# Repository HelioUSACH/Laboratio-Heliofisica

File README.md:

Rama principal "Main"
Subir avances en ramas secundarias que se deben crear

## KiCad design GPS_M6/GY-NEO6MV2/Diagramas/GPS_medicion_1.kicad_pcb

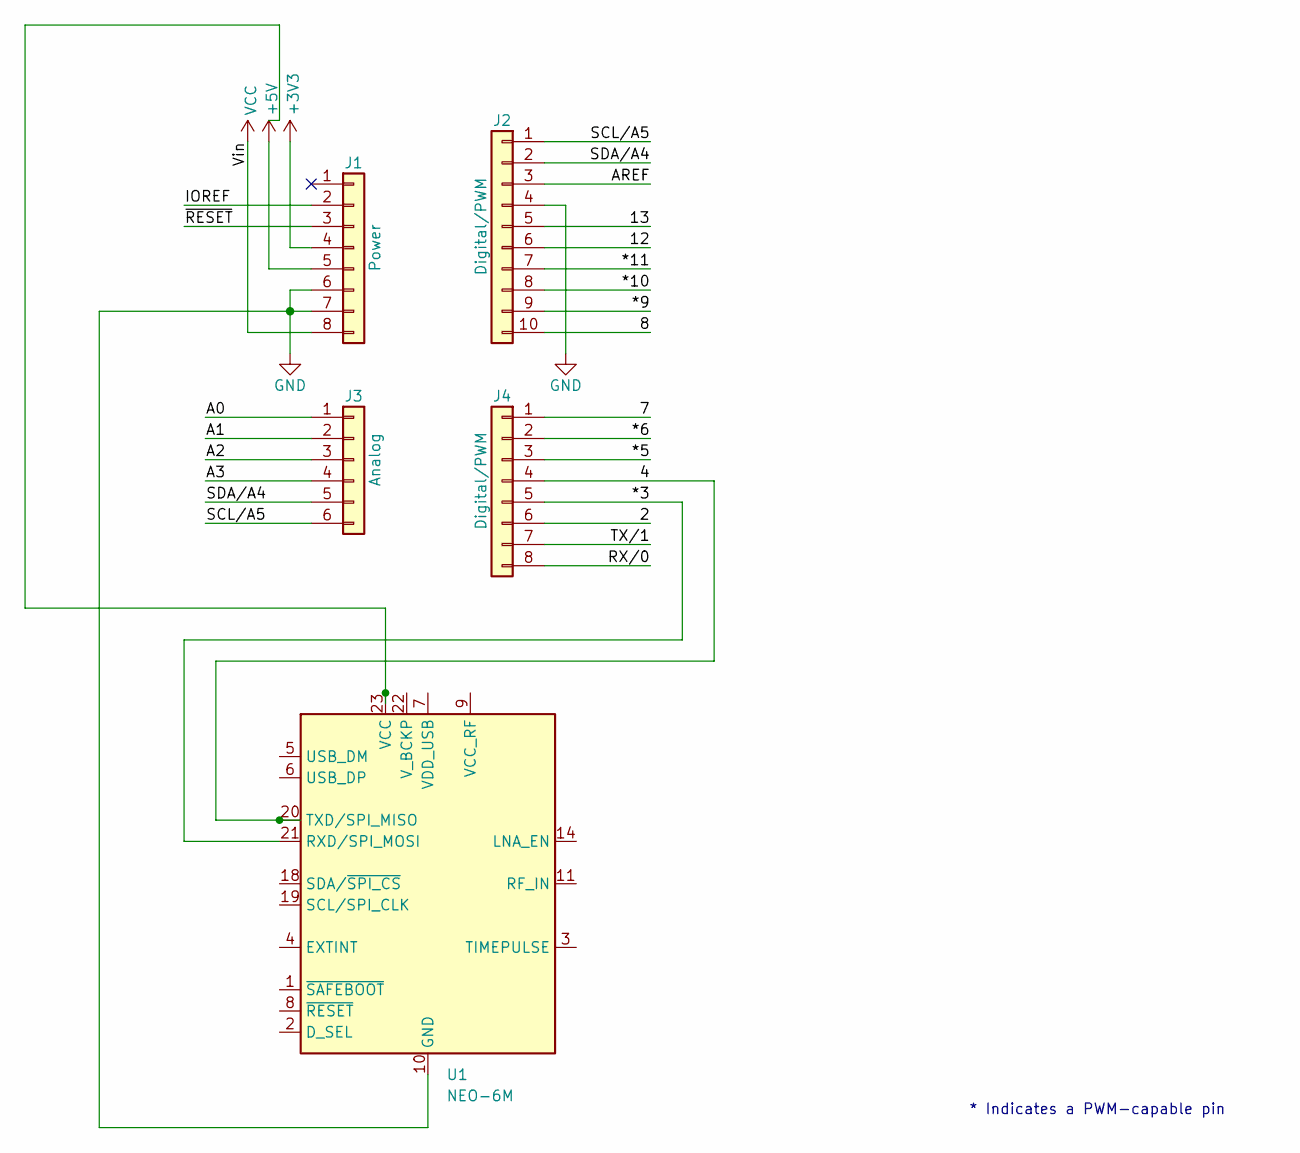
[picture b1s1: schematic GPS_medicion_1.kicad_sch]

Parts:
J1: Power; PinSocket_1x08_P2.54mm_Vertical
J2: Digital/PWM; PinSocket_1x10_P2.54mm_Vertical
J3: Analog; PinSocket_1x06_P2.54mm_Vertical
J4: Digital/PWM; PinSocket_1x08_P2.54mm_Vertical
U1: NEO-6M; ublox_NEO

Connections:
+3V3: J1.4
+5V: J1.5
/2: J4.6
/4: J4.4, U1.20 (TXD/SPI_MISO)
/7: J4.1
/8: J2.10
/12: J2.6
/13: J2.5
/*3: J4.5, U1.21 (RXD/SPI_MOSI)
/*5: J4.3
/*6: J4.2
/*9: J2.9
/*10: J2.8
/*11: J2.7
/A0: J3.1
/A1: J3.2
/A2: J3.3
/A3: J3.4
/AREF: J2.3
/IOREF: J1.2
/RX/0: J4.8
/SCL/A5: J2.1, J3.6
/SDA/A4: J2.2, J3.5
/TX/1: J4.7
/~RESET: J1.3
GND: J1.6, J1.7, J2.4, U1.10 (GND), U1.12 (GND), U1.13 (GND), U1.24 (GND)
VCC: J1.8

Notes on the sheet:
* Indicates a PWM-capable pin

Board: 2 copper layers, 9 parts (0 on the bottom side), 5 nets, no tracks yet.

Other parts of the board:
MH1, MH2, MH3, MH4: MountingHole_3.2mm
